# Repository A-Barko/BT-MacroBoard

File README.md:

# WEEKEND PROJECT 1 - Macro keyboard 
first of a series of simple projects to be done in one or 2 weekend not accounting shipping.
## Macro keyboard specifications
4x4 switch matrix
2 potentiometer for dial
Bluetooth 
USB-C
Battery Powered 
e ink screen
ambiant temprature sensor

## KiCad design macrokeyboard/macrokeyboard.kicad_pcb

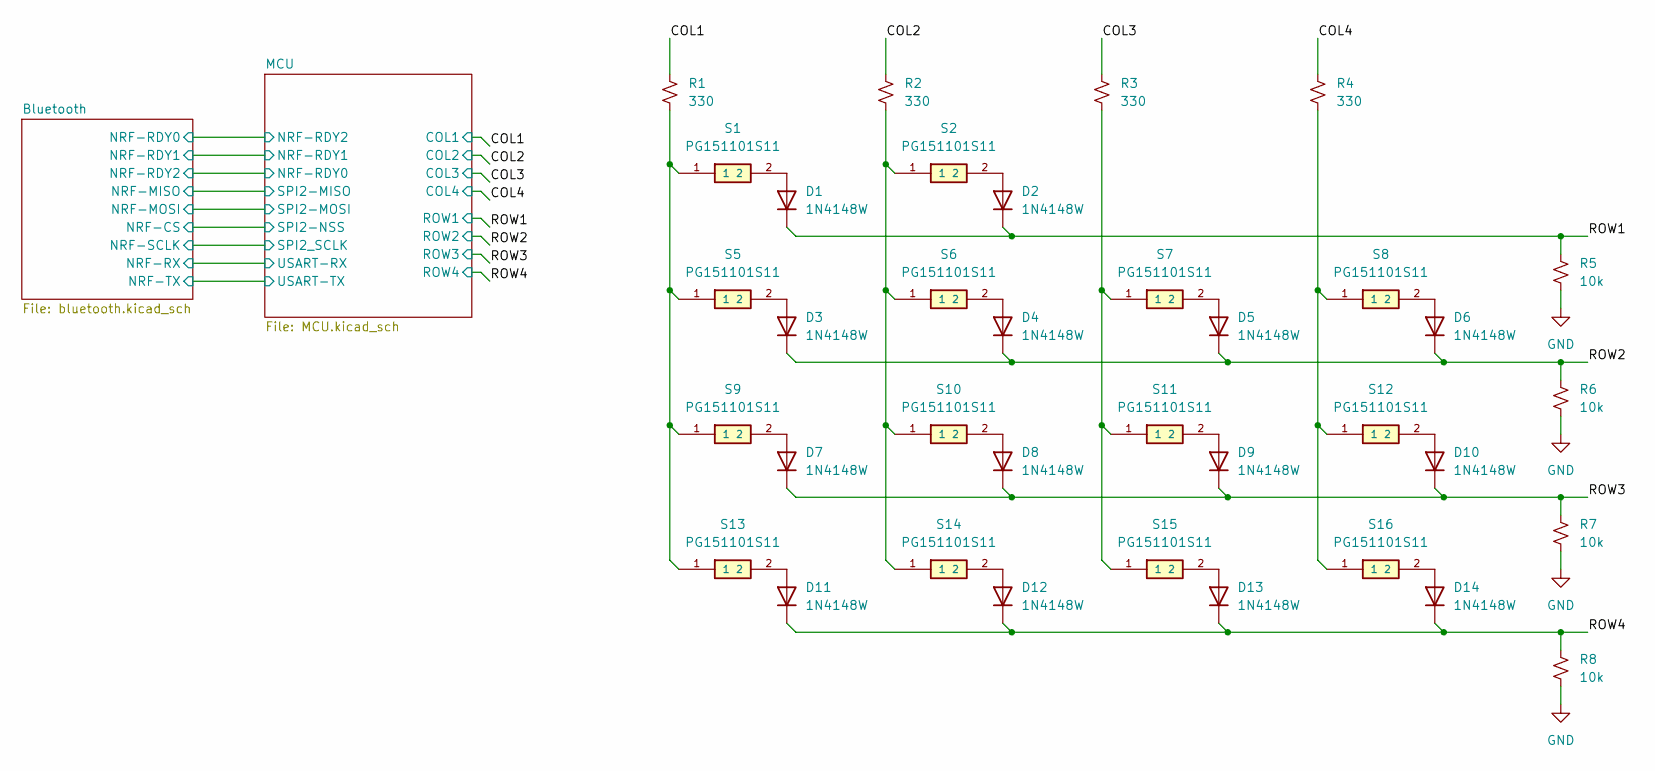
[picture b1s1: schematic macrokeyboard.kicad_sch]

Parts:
D1, D2, D3, D4, D5, D6, D7, D8, D9, D10, D11, D12, D13, D14: 1N4148W; D_SOD-123
R1, R2, R3, R4: 330; R_0603_1608Metric
R5, R6, R7, R8: 10k; R_0603_1608Metric
S1, S2, S5, S6, S7, S8, S9, S10, S11, S12, S13, S14, S15, S16: PG151101S11; Kailh_socket_MX; PARTREV A

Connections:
/COL1: R1.2; also elsewhere on the board
/COL2: R2.2; also elsewhere on the board
/COL3: R3.2; also elsewhere on the board
/COL4: R4.2; also elsewhere on the board
/ROW1: D1.1 (K), D2.1 (K), R5.1; also elsewhere on the board
/ROW2: D3.1 (K), D4.1 (K), D5.1 (K), D6.1 (K), R6.1; also elsewhere on the board
/ROW3: D7.1 (K), D8.1 (K), D9.1 (K), D10.1 (K), R7.1; also elsewhere on the board
/ROW4: D11.1 (K), D12.1 (K), D13.1 (K), D14.1 (K), R8.1; also elsewhere on the board
GND: R5.2, R6.2, R7.2, R8.2; also elsewhere on the board
unnamed: D1.2 (A), S1.2
unnamed: D2.2 (A), S2.2
unnamed: D3.2 (A), S5.2
unnamed: D4.2 (A), S6.2
unnamed: D5.2 (A), S7.2
unnamed: D6.2 (A), S8.2
unnamed: D7.2 (A), S9.2
unnamed: D8.2 (A), S10.2
unnamed: D9.2 (A), S11.2
unnamed: D10.2 (A), S12.2
unnamed: D11.2 (A), S13.2
unnamed: D12.2 (A), S14.2
unnamed: D13.2 (A), S15.2
unnamed: D14.2 (A), S16.2
unnamed: R1.1, S1.1, S5.1, S9.1, S13.1
unnamed: R2.1, S2.1, S6.1, S10.1, S14.1
unnamed: R3.1, S7.1, S11.1, S15.1
unnamed: R4.1, S8.1, S12.1, S16.1

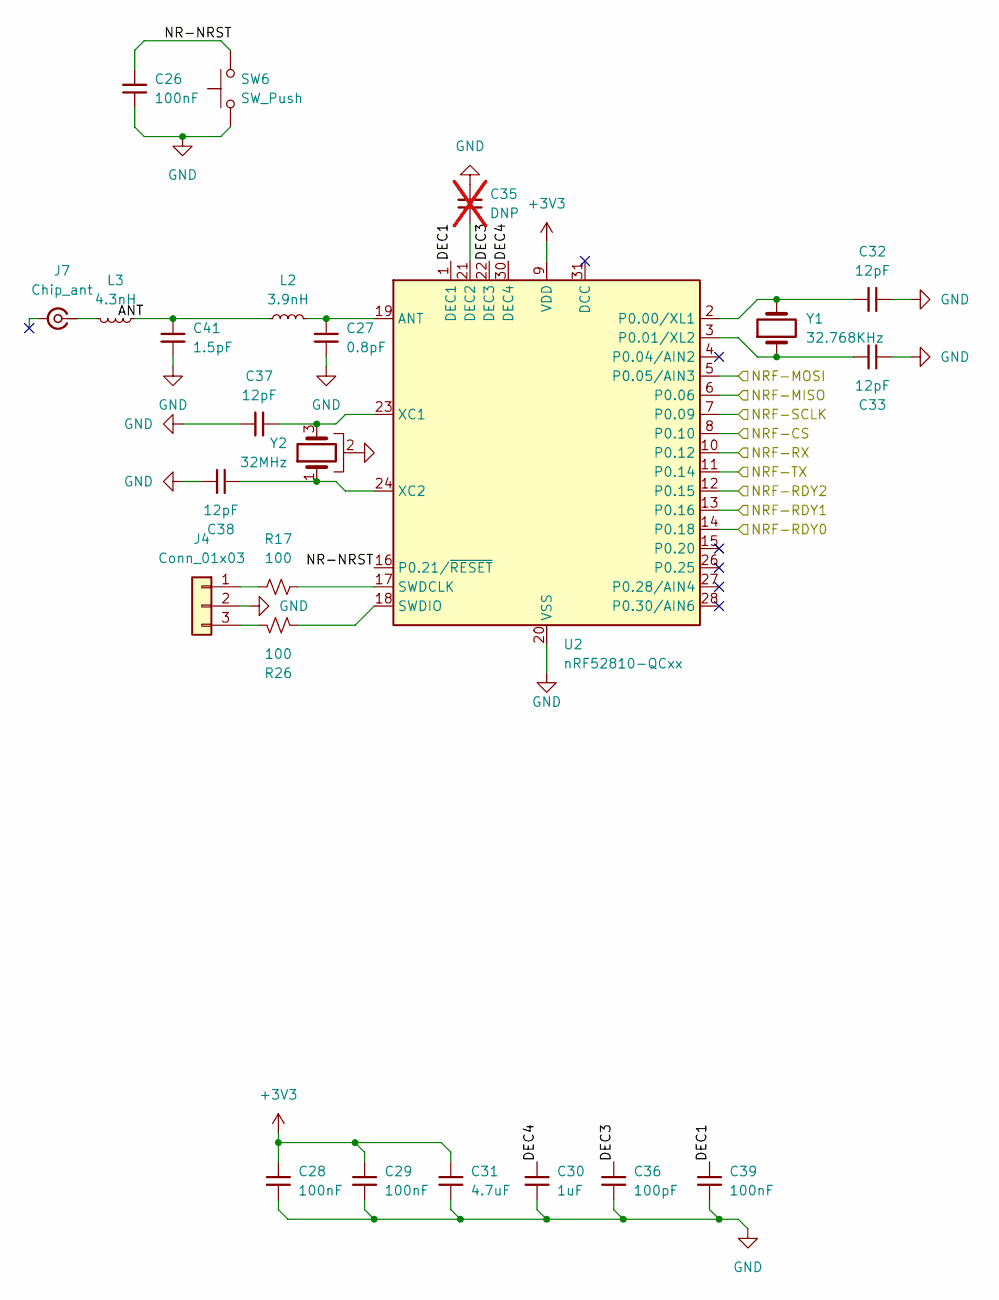
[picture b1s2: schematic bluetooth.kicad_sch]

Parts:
C26, C28, C29, C39: 100nF; C_0603_1608Metric
C27: 0.8pF; C_0402_1005Metric
C30: 1uF; C_0603_1608Metric
C31: 4.7uF; C_0603_1608Metric
C32, C33, C37, C38: 12pF; C_0603_1608Metric
C35: DNP; C_0603_1608Metric; not fitted
C36: 100pF; C_0603_1608Metric
C41: 1.5pF; C_0402_1005Metric
J4: Conn_01x03; PinHeader_1x03_P2.54mm_Vertical
J7: Chip_ant; KH5220-A36
L2: 3.9nH; L_0402_1005Metric
L3: 4.3nH; L_0402_1005Metric
R17, R26: 100; R_0603_1608Metric
SW6: SW_Push; button_smol
U2: nRF52810-QCxx; QFN-32-1EP_5x5mm_P0.5mm_EP3.6x3.6mm
Y1: 32.768KHz; Crystal_SMD_3215-2Pin_3.2x1.5mm
Y2: 32MHz; Crystal_SMD_2520-4Pin_2.5x2.0mm

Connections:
+3V3: C28.1, C29.1, C31.1, U2.9 (VDD), U2.25 (VDD), U2.32 (VDD); also elsewhere on the board
/Bluetooth/ANT: C41.2, L2.1, L3.1
/Bluetooth/DEC1: C39.2, U2.1 (DEC1)
/Bluetooth/DEC3: C36.2, U2.22 (DEC3)
/Bluetooth/DEC4: C30.1, U2.30 (DEC4)
/Bluetooth/NR-NRST: C26.2, SW6.2, U2.16 (P0.21/~RESET)
/Bluetooth/NRF-CS: U2.8 (P0.10); also elsewhere on the board
/Bluetooth/NRF-MISO: U2.6 (P0.06); also elsewhere on the board
/Bluetooth/NRF-MOSI: U2.5 (P0.05/AIN3); also elsewhere on the board
/Bluetooth/NRF-RDY0: U2.14 (P0.18); also elsewhere on the board
/Bluetooth/NRF-RDY1: U2.13 (P0.16); also elsewhere on the board
/Bluetooth/NRF-RDY2: U2.12 (P0.15); also elsewhere on the board
/Bluetooth/NRF-RX: U2.10 (P0.12); also elsewhere on the board
/Bluetooth/NRF-SCLK: U2.7 (P0.09); also elsewhere on the board
/Bluetooth/NRF-TX: U2.11 (P0.14); also elsewhere on the board
GND: C26.1, C27.1, C28.2, C29.2, C30.2, C31.2, C32.2, C33.2, C35.2, C36.1, C37.2, C38.2, C39.1, C41.1, J4.2, SW6.1, U2.20 (VSS), U2.29 (VSS), U2.33 (VSS), Y2.2; also elsewhere on the board
unnamed: J4.1, R17.1
unnamed: J4.3, R26.1
unnamed: J7.1 (In_1), L3.2
unnamed: C27.2, L2.2, U2.19 (ANT)
unnamed: C35.1, U2.21 (DEC2)
unnamed: C32.1, U2.2 (P0.00/XL1), Y1.2
unnamed: C33.1, U2.3 (P0.01/XL2), Y1.1
unnamed: R17.2, U2.17 (SWDCLK)
unnamed: R26.2, U2.18 (SWDIO)
unnamed: C37.1, U2.23 (XC1), Y2.3
unnamed: C38.1, U2.24 (XC2), Y2.1

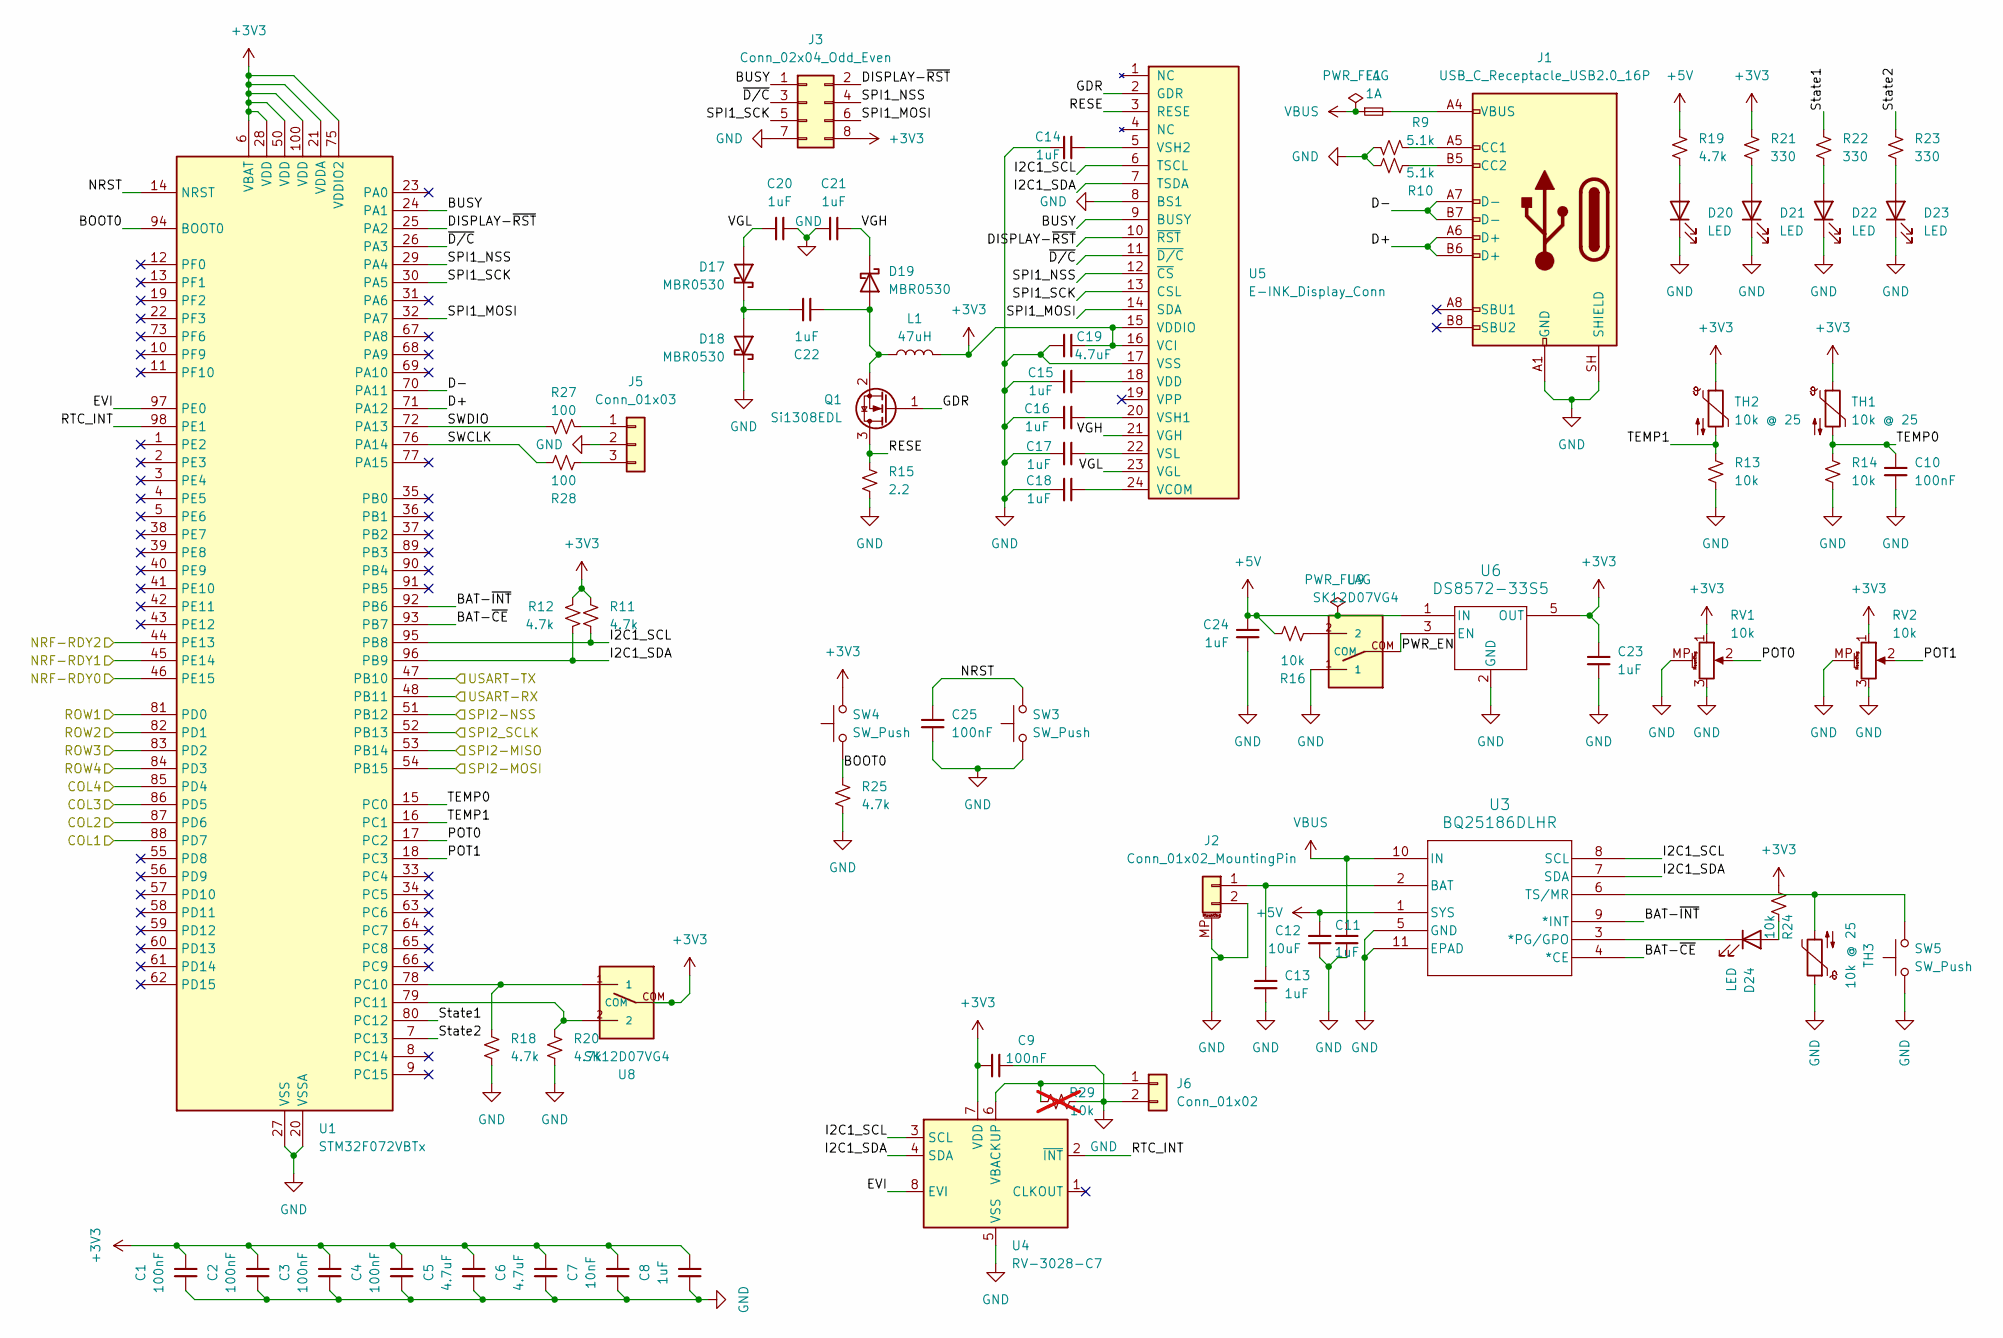
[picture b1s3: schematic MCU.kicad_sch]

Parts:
C1, C2, C3, C4, C9, C10, C25: 100nF; C_0603_1608Metric
C5, C6, C19: 4.7uF; C_0603_1608Metric
C7: 10nF; C_0603_1608Metric
C8, C11, C13, C14, C15, C16, C17, C18, C20, C21, C22, C23, C24: 1uF; C_0603_1608Metric
C12: 10uF; C_0603_1608Metric
D17, D18, D19: MBR0530; D_SOD-123
D20, D21, D22, D23, D24: LED; LED_0603_1608Metric
F1: 1A; Fuse_0603_1608Metric
J1: USB_C_Receptacle_USB2.0_16P; USB_C_Receptacle_HCTL_HC-TYPE-C-16P-01A
J2: Conn_01x02_MountingPin; JST_PH_S2B-PH-K_1x02_P2.00mm_Horizontal
J3: Conn_02x04_Odd_Even; PinHeader_2x04_P2.54mm_Vertical
J5: Conn_01x03; PinHeader_1x03_P2.54mm_Vertical
J6: Conn_01x02; PinHeader_1x02_P2.00mm_Vertical
L1: 47uH; L_Neosid_SM-PIC0612H
Q1: Si1308EDL; SOT-323_SC-70
R9, R10: 5.1k; R_0603_1608Metric
R11, R12, R18, R19, R20, R25: 4.7k; R_0603_1608Metric
R13, R14, R16, R24: 10k; R_0603_1608Metric
R15: 2.2; R_0603_1608Metric
R21, R22, R23: 330; R_0603_1608Metric
R27, R28: 100; R_0603_1608Metric
R29: 10k; R_0603_1608Metric; not fitted
RV1, RV2: 10k; RK09K1130AH1_AAL
SW3, SW4, SW5: SW_Push; button_smol
TH1, TH2: 10k @ 25; R_0603_1608Metric
TH3: 10k @ 25; R_0805_2012Metric
U1: STM32F072VBTx; LQFP-100_14x14mm_P0.5mm
U3: BQ25186DLHR; WSON10_2P2X2_TEX
U4: RV-3028-C7; MicroCrystal_C7_SON-8_1.5x3.2mm_P0.9mm
U5: E-INK_Display_Conn; AMPHENOL_F3311A7H121024E200
U6: DS8572-33S5; SOT_233DBVR_TEX
U8, U9: SK12D07VG4

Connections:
+3V3: C1.2, C2.2, C3.2, C4.2, C5.2, C6.2, C7.2, C8.2, C9.1, C19.2, C23.1, J3.8, L1.2, R11.2, R12.2, R21.1, R24.2, RV1.1, RV2.1, SW4.2, TH1.1, TH2.1, U1.6 (VBAT), U1.21 (VDDA), U1.28 (VDD), U1.50 (VDD), U1.75 (VDDIO2), U1.100 (VDD), U4.7 (VDD), U5.15 (VDDIO), U5.16 (VCI), U6.5 (OUT), U8.COM; also elsewhere on the board
+5V: C12.1, C24.1, R16.1, R19.1, U3.1 (SYS), U6.1 (IN)
/MCU/BAT-~CE: U1.93 (PB7), U3.4 (*CE); also elsewhere on the board
/MCU/BAT-~INT: U1.92 (PB6), U3.9 (*INT); also elsewhere on the board
/MCU/BOOT0: R25.1, SW4.1, U1.94 (BOOT0); also elsewhere on the board
/MCU/BUSY: J3.1, U1.24 (PA1), U5.9 (BUSY); also elsewhere on the board
/MCU/D+: J1.A6 (D+), J1.B6 (D+), U1.71 (PA12); also elsewhere on the board
/MCU/D-: J1.A7 (D-), J1.B7 (D-), U1.70 (PA11); also elsewhere on the board
/MCU/DISPLAY-~RST: J3.2, U1.25 (PA2), U5.10 (~RST); also elsewhere on the board
/MCU/EVI: U1.97 (PE0), U4.8 (EVI); also elsewhere on the board
/MCU/GDR: Q1.1 (G), U5.2 (GDR)
/MCU/I2C1_SCL: R11.1, U1.95 (PB8), U3.8 (SCL), U4.3 (SCL), U5.6 (TSCL); also elsewhere on the board
/MCU/I2C1_SDA: R12.1, U1.96 (PB9), U3.7 (SDA), U4.4 (SDA), U5.7 (TSDA); also elsewhere on the board
/MCU/NRST: C25.2, SW3.2, U1.14 (NRST); also elsewhere on the board
/MCU/POT0: RV1.2, U1.17 (PC2); also elsewhere on the board
/MCU/POT1: RV2.2, U1.18 (PC3); also elsewhere on the board
/MCU/PWR_EN: U6.3 (EN), U9.COM
/MCU/RESE: Q1.3 (D), R15.2, U5.3 (RESE)
/MCU/RTC_INT: U1.98 (PE1), U4.2 (~INT); also elsewhere on the board
/MCU/SPI1_MOSI: J3.6, U1.32 (PA7), U5.14 (SDA); also elsewhere on the board
/MCU/SPI1_NSS: J3.4, U1.29 (PA4), U5.12 (~CS); also elsewhere on the board
/MCU/SPI1_SCK: J3.5, U1.30 (PA5), U5.13 (CSL); also elsewhere on the board
/MCU/SWCLK: R28.2, U1.76 (PA14); also elsewhere on the board
/MCU/SWDIO: R27.2, U1.72 (PA13); also elsewhere on the board
/MCU/State1: R22.1, U1.80 (PC12); also elsewhere on the board
/MCU/State2: R23.1, U1.7 (PC13); also elsewhere on the board
/MCU/TEMP0: C10.1, R14.1, TH1.2, U1.15 (PC0); also elsewhere on the board
/MCU/TEMP1: R13.1, TH2.2, U1.16 (PC1); also elsewhere on the board
/MCU/VGH: C21.2, D19.1 (K), U5.21 (VGH)
/MCU/VGL: C20.1, D17.2 (A), U5.23 (VGL)
/MCU/~D/C: J3.3, U1.26 (PA3), U5.11 (~D/C); also elsewhere on the board
GND: C1.1, C2.1, C3.1, C4.1, C5.1, C6.1, C7.1, C8.1, C9.2, C10.2, C11.2, C12.2, C13.2, C14.2, C15.2, C16.2, C17.2, C18.2, C19.1, C20.2, C21.1, C23.2, C24.2, C25.1, D18.1 (K), D20.1 (K), D21.1 (K), D22.1 (K), D23.1 (K), J1.A1 (GND), J1.A12 (GND), J1.B1 (GND), J1.B12 (GND), J1.SH (SHIELD), J2.2, J2.MP (MountPin), J3.7, J5.2, J6.2, R9.2, R10.2, R13.2, R14.2, R15.1, R18.2, R20.2, R25.2, R29.1, RV1.3, RV1.MP (MountPin), RV2.3, RV2.MP (MountPin), SW3.1, SW5.1, TH3.1, U1.20 (VSSA), U1.27 (VSS), U1.49 (VSS), U1.74 (VSS), U1.99 (VSS), U3.5 (GND), U3.11 (EPAD), U4.5 (VSS), U5.8 (BS1), U5.17 (VSS), U6.2 (GND), U9.1; also elsewhere on the board
unnamed: C22.1, D17.1 (K), D18.2 (A)
unnamed: C22.2, D19.2 (A), L1.1, Q1.2 (S)
unnamed: D20.2 (A), R19.2
unnamed: D21.2 (A), R21.2
unnamed: D22.2 (A), R22.2
unnamed: D23.2 (A), R23.2
unnamed: D24.2 (A), R24.1
unnamed: D24.1 (K), U3.3 (*PG/GPO)
unnamed: F1.2, J1.A4 (VBUS), J1.A9 (VBUS), J1.B4 (VBUS), J1.B9 (VBUS)
unnamed: J1.A5 (CC1), R9.1
unnamed: J1.B5 (CC2), R10.1
unnamed: C13.1, J2.1, U3.2 (BAT)
unnamed: J5.1, R27.1
unnamed: J5.3, R28.1
unnamed: J6.1, R29.2, U4.6 (VBACKUP)
unnamed: R16.2, U9.2
unnamed 91: R18.1, U1.78 (PC10), U8.1; also elsewhere on the board
unnamed 92: R20.1, U1.79 (PC11), U8.2; also elsewhere on the board
unnamed: SW5.2, TH3.2, U3.6 (TS/MR)
unnamed: C18.1, U5.24 (VCOM)
unnamed: C15.1, U5.18 (VDD)
unnamed: C16.1, U5.20 (VSH1)
unnamed: C14.1, U5.5 (VSH2)
unnamed: C17.1, U5.22 (VSL)
VBUS: C11.1, F1.1, U3.10 (IN)

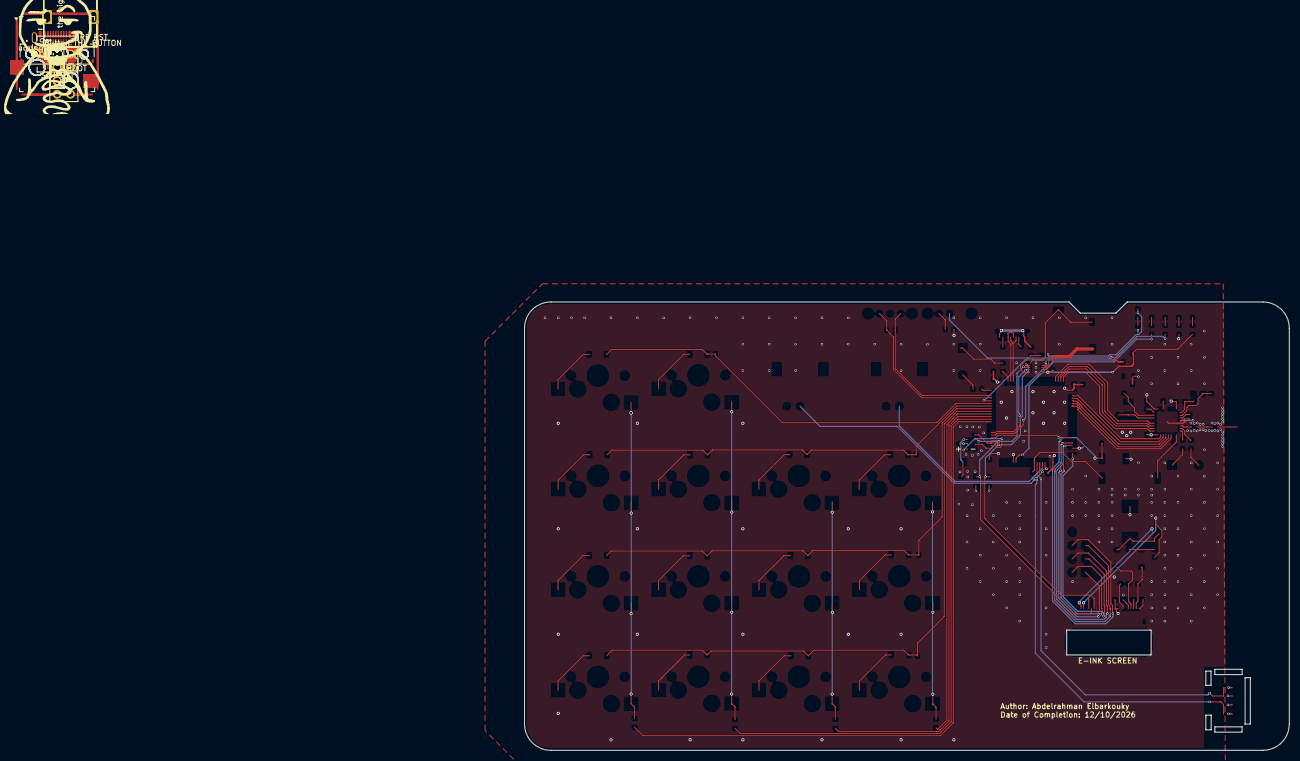
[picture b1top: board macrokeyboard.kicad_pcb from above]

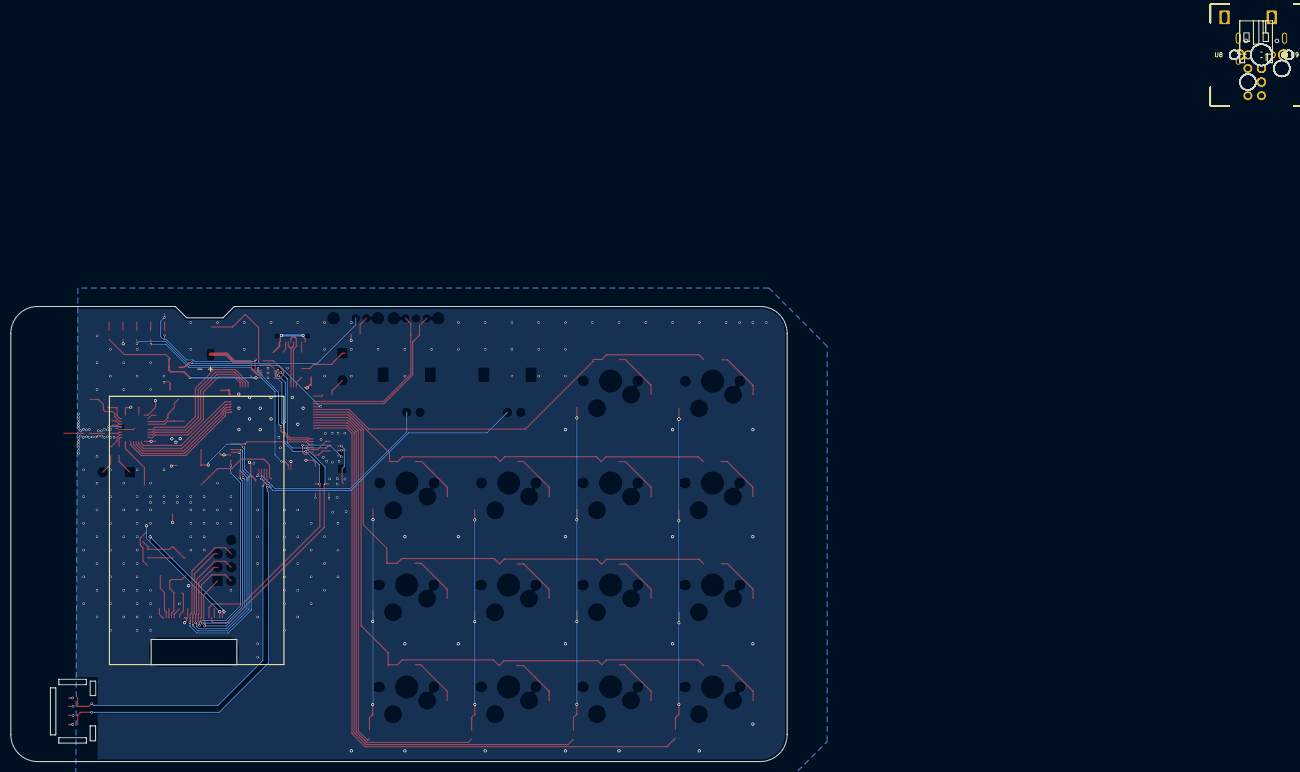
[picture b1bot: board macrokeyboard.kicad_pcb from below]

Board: 4 copper layers, 145.0 x 85.0 mm, 135 parts (2 on the bottom side), 108 nets.

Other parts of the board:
the big man: STM32F072VBTx; LQFP-100_14x14mm_P0.5mm

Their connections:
+3V3: the big man.6 (VBAT), the big man.21 (VDDA), the big man.28 (VDD), the big man.50 (VDD), the big man.75 (VDDIO2), the big man.100 (VDD); also elsewhere on the board
/Bluetooth/NRF-CS: the big man.51 (PB12); also elsewhere on the board
/Bluetooth/NRF-MISO: the big man.53 (PB14); also elsewhere on the board
/Bluetooth/NRF-MOSI: the big man.54 (PB15); also elsewhere on the board
/Bluetooth/NRF-RDY0: the big man.44 (PE13); also elsewhere on the board
/Bluetooth/NRF-RDY1: the big man.45 (PE14); also elsewhere on the board
/Bluetooth/NRF-RDY2: the big man.46 (PE15); also elsewhere on the board
/Bluetooth/NRF-RX: the big man.48 (PB11); also elsewhere on the board
/Bluetooth/NRF-SCLK: the big man.52 (PB13); also elsewhere on the board
/Bluetooth/NRF-TX: the big man.47 (PB10); also elsewhere on the board
/COL1: the big man.88 (PD7); also elsewhere on the board
/COL2: the big man.87 (PD6); also elsewhere on the board
/COL3: the big man.86 (PD5); also elsewhere on the board
/COL4: the big man.85 (PD4); also elsewhere on the board
/MCU/BAT-~CE: the big man.93 (PB7); also elsewhere on the board
/MCU/BAT-~INT: the big man.92 (PB6); also elsewhere on the board
/MCU/BOOT0: the big man.94 (BOOT0); also elsewhere on the board
/MCU/BUSY: the big man.24 (PA1); also elsewhere on the board
/MCU/D+: the big man.71 (PA12); also elsewhere on the board
/MCU/D-: the big man.70 (PA11); also elsewhere on the board
/MCU/DISPLAY-~RST: the big man.25 (PA2); also elsewhere on the board
/MCU/EVI: the big man.97 (PE0); also elsewhere on the board
/MCU/I2C1_SCL: the big man.95 (PB8); also elsewhere on the board
/MCU/I2C1_SDA: the big man.96 (PB9); also elsewhere on the board
/MCU/NRST: the big man.14 (NRST); also elsewhere on the board
/MCU/POT0: the big man.17 (PC2); also elsewhere on the board
/MCU/POT1: the big man.18 (PC3); also elsewhere on the board
/MCU/RTC_INT: the big man.98 (PE1); also elsewhere on the board
/MCU/SPI1_MOSI: the big man.32 (PA7); also elsewhere on the board
/MCU/SPI1_NSS: the big man.29 (PA4); also elsewhere on the board
/MCU/SPI1_SCK: the big man.30 (PA5); also elsewhere on the board
/MCU/SWCLK: the big man.76 (PA14); also elsewhere on the board
/MCU/SWDIO: the big man.72 (PA13); also elsewhere on the board
/MCU/State1: the big man.80 (PC12); also elsewhere on the board
/MCU/State2: the big man.7 (PC13); also elsewhere on the board
/MCU/TEMP0: the big man.15 (PC0); also elsewhere on the board
/MCU/TEMP1: the big man.16 (PC1); also elsewhere on the board
/MCU/~D/C: the big man.26 (PA3); also elsewhere on the board
/ROW1: the big man.81 (PD0); also elsewhere on the board
/ROW2: the big man.82 (PD1); also elsewhere on the board
/ROW3: the big man.83 (PD2); also elsewhere on the board
/ROW4: the big man.84 (PD3); also elsewhere on the board
GND: the big man.20 (VSSA), the big man.27 (VSS), the big man.49 (VSS), the big man.74 (VSS), the big man.99 (VSS); also elsewhere on the board
unnamed 91: the big man.78 (PC10); also elsewhere on the board
unnamed 92: the big man.79 (PC11); also elsewhere on the board

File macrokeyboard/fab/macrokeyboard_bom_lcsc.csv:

"Quantity","Value","Designator","Footprint","LCSC Part Number"
"11","100nF","C1,C2,C3,C4,C9,C10,C25,C26,C28,C29,C39","Capacitor_SMD:C_0603_1608Metric",""
"4","4.7uF","C5,C6,C19,C31","Capacitor_SMD:C_0603_1608Metric",""
"1","10nF","C7","Capacitor_SMD:C_0603_1608Metric",""
"14","1uF","C8,C11,C13,C14,C15,C16,C17,C18,C20,C21,C22,C23,C24,C30","Capacitor_SMD:C_0603_1608Metric",""
"1","10uF","C12","Capacitor_SMD:C_0603_1608Metric",""
"1","0.8pF","C27","Capacitor_SMD:C_0402_1005Metric",""
"4","12pF","C32,C33,C37,C38","Capacitor_SMD:C_0603_1608Metric",""
"1","100pF","C36","Capacitor_SMD:C_0603_1608Metric",""
"1","1.5pF","C41","Capacitor_SMD:C_0402_1005Metric",""
"14","1N4148W","D1,D2,D3,D4,D5,D6,D7,D8,D9,D10,D11,D12,D13,D14","Diode_SMD:D_SOD-123",""
"3","MBR0530","D17,D18,D19","Diode_SMD:D_SOD-123",""
"5","LED","D20,D21,D22,D23,D24","LED_SMD:LED_0603_1608Metric",""
"1","1A","F1","Fuse:Fuse_0603_1608Metric",""
"1","USB_C_Receptacle_USB2.0_16P","J1","Connector_USB:USB_C_Receptacle_HCTL_HC-TYPE-C-16P-01A",""
"1","Conn_01x02_MountingPin","J2","Connector_JST:JST_PH_S2B-PH-K_1x02_P2.00mm_Horizontal",""
"1","Conn_02x04_Odd_Even","J3","Connector_PinHeader_2.54mm:PinHeader_2x04_P2.54mm_Vertical",""
"2","Conn_01x03","J4,J5","Connector_PinHeader_2.54mm:PinHeader_1x03_P2.54mm_Vertical",""
"1","Conn_01x02","J6","Connector_PinHeader_2.00mm:PinHeader_1x02_P2.00mm_Vertical",""
"1","Chip_ant","J7","1_macrokeys:KH5220-A36",""
"1","47uH","L1","Inductor_SMD:L_Neosid_SM-PIC0612H",""
"1","3.9nH","L2","Inductor_SMD:L_0402_1005Metric",""
"1","4.3nH","L3","Inductor_SMD:L_0402_1005Metric",""
"1","Si1308EDL","Q1","Package_TO_SOT_SMD:SOT-323_SC-70",""
"7","330","R1,R2,R3,R4,R21,R22,R23","Resistor_SMD:R_0603_1608Metric",""
"8","10k","R5,R6,R7,R8,R13,R14,R16,R24","Resistor_SMD:R_0603_1608Metric",""
"2","5.1k","R9,R10","Resistor_SMD:R_0603_1608Metric",""
"6","4.7k","R11,R12,R18,R19,R20,R25","Resistor_SMD:R_0603_1608Metric",""
"1","2.2","R15","Resistor_SMD:R_0603_1608Metric",""
"4","100","R17,R26,R27,R28","Resistor_SMD:R_0603_1608Metric",""
"2","10k","RV1,RV2","1_macrokeys:RK09K1130AH1_AAL",""
"14","PG151101S11","S1,S2,S5,S6,S7,S8,S9,S10,S11,S12,S13,S14,S15,S16","1_macrokeys:Kailh_socket_MX",""
"4","SW_Push","SW3,SW4,SW5,SW6","1_macrokeys:button_smol",""
"2","10k @ 25","TH1,TH2","Resistor_SMD:R_0603_1608Metric",""
"1","10k @ 25","TH3","Resistor_SMD:R_0805_2012Metric",""
"1","STM32F072VBTx","U1","Package_QFP:LQFP-100_14x14mm_P0.5mm",""
"1","nRF52810-QCxx","U2","Package_DFN_QFN:QFN-32-1EP_5x5mm_P0.5mm_EP3.6x3.6mm",""
"1","BQ25186DLHR","U3","1_macrokeys:WSON10_2P2X2_TEX",""
"1","RV-3028-C7","U4","Package_SON:MicroCrystal_C7_SON-8_1.5x3.2mm_P0.9mm",""
"1","E-INK_Display_Conn","U5","1_macrokeys:AMPHENOL_F3311A7H121024E200",""
"1","DS8572-33S5","U6","1_macrokeys:SOT_233DBVR_TEX",""
"2","SK12D07VG4","U8,U9","1_macrokeys:SK12D07VG4",""
"1","32.768KHz","Y1","Crystal:Crystal_SMD_3215-2Pin_3.2x1.5mm",""
"1","32MHz","Y2","Crystal:Crystal_SMD_2520-4Pin_2.5x2.0mm",""
